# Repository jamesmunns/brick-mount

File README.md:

# Brick Boards

Boards designed to be compatible with LEGO and other plastic building blocks.

There are KiCAD footprints for a variety of different brick arrangements in [the parts folder](./parts/brick-4_9id-6_0od.pretty/). I've also included a number of personal projects using these footprints in the `boards/` folder.

## LICENSE

The contents of the `parts/brick-4_9id-6_0od.pretty/` folder are licensed under a CC0 license.

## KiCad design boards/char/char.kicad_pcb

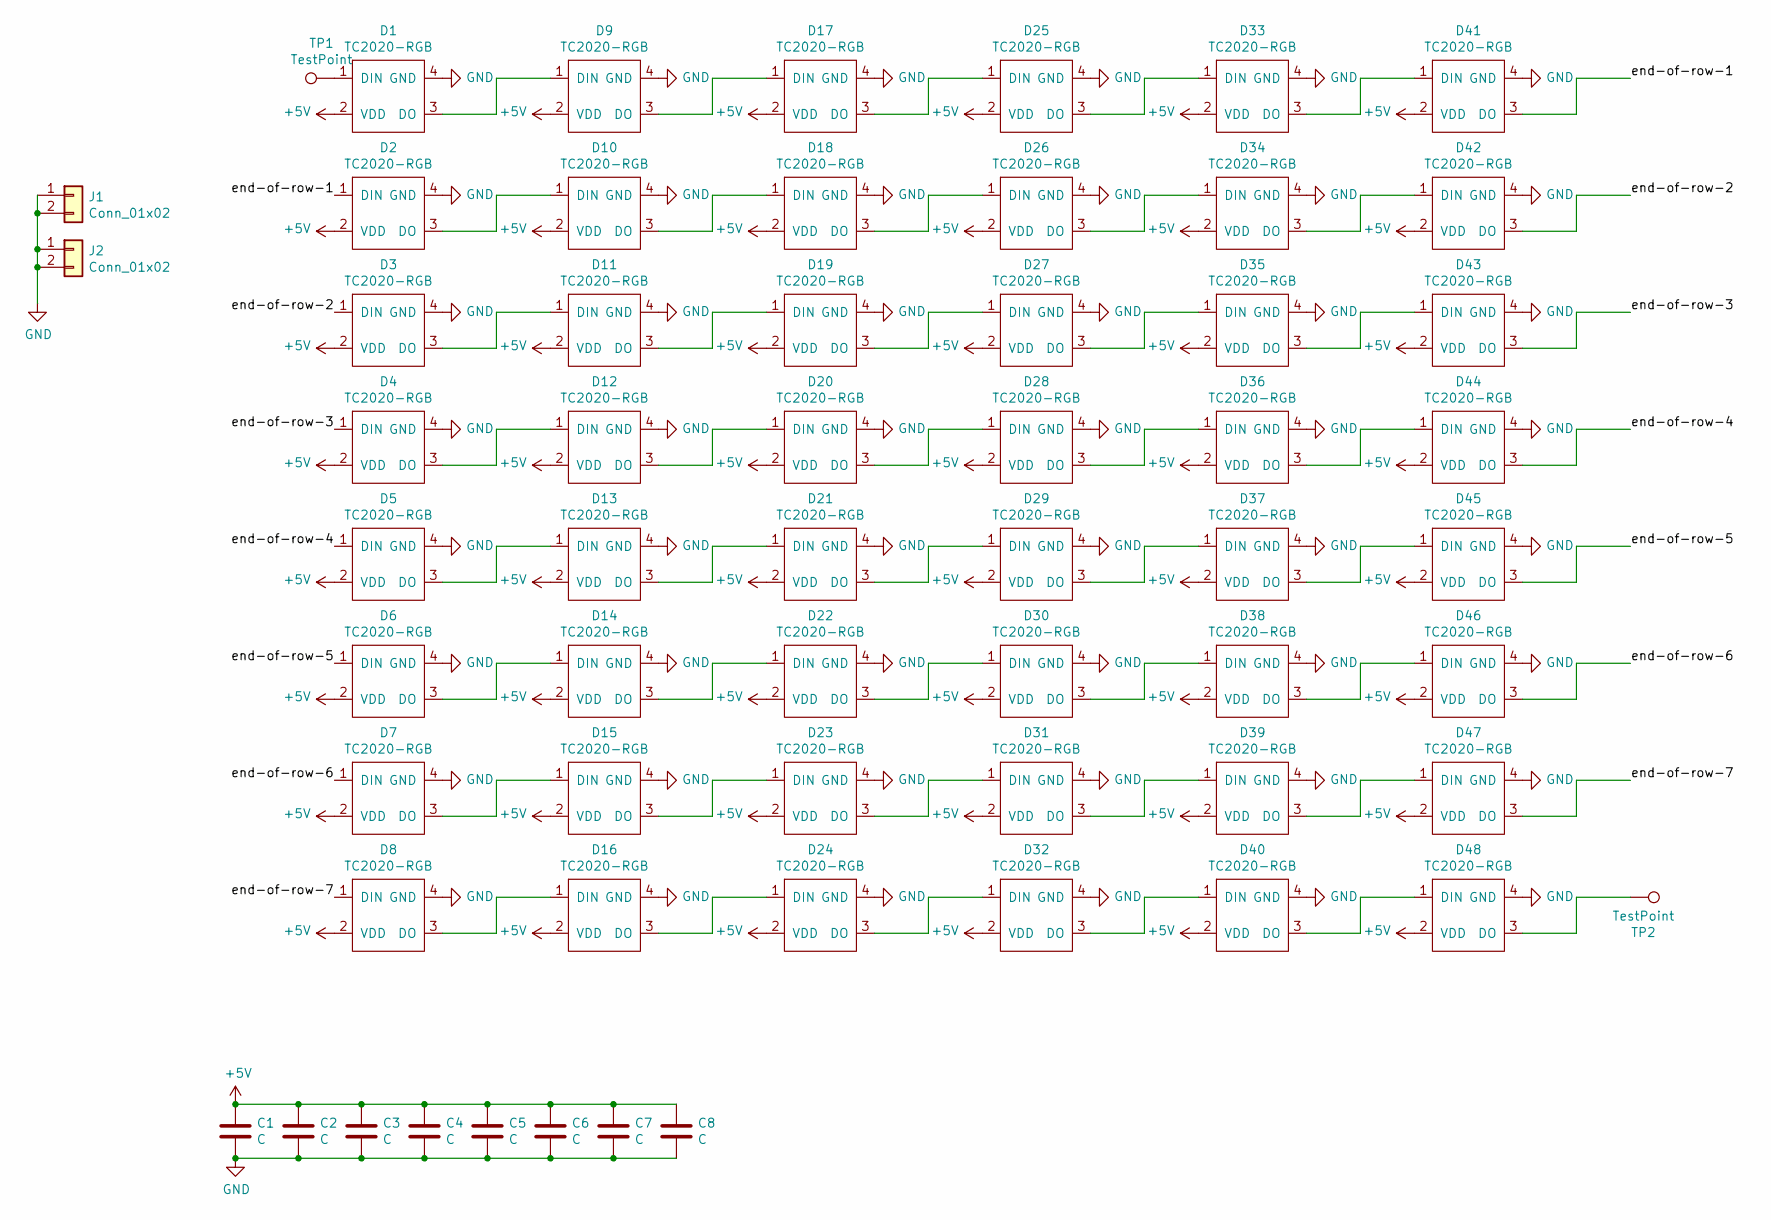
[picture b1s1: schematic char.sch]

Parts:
C1, C2, C3, C4, C5, C6, C7, C8: C; C_0805_2012Metric_Pad1.18x1.45mm_HandSolder
D1, D2, D3, D4, D5, D6, D7, D8, D9, D10, D11, D12, D13, D14, D15, D16, D17, D18, D19, D20, D21, D22, D23, D24, D25, D26, D27, D28, D29, D30, D31, D32, D33, D34, D35, D36, D37, D38, D39, D40, D41, D42, D43, D44, D45, D46, D47, D48: TC2020-RGB; TC2020RGB
J1, J2: Conn_01x02; brick-1x2
TP1, TP2: TestPoint; TestPoint_Pad_D1.5mm

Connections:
+5V: C1.1, C2.1, C3.1, C4.1, C5.1, C6.1, C7.1, C8.1, D1.2 (VDD), D2.2 (VDD), D3.2 (VDD), D4.2 (VDD), D5.2 (VDD), D6.2 (VDD), D7.2 (VDD), D8.2 (VDD), D9.2 (VDD), D10.2 (VDD), D11.2 (VDD), D12.2 (VDD), D13.2 (VDD), D14.2 (VDD), D15.2 (VDD), D16.2 (VDD), D17.2 (VDD), D18.2 (VDD), D19.2 (VDD), D20.2 (VDD), D21.2 (VDD), D22.2 (VDD), D23.2 (VDD), D24.2 (VDD), D25.2 (VDD), D26.2 (VDD), D27.2 (VDD), D28.2 (VDD), D29.2 (VDD), D30.2 (VDD), D31.2 (VDD), D32.2 (VDD), D33.2 (VDD), D34.2 (VDD), D35.2 (VDD), D36.2 (VDD), D37.2 (VDD), D38.2 (VDD), D39.2 (VDD), D40.2 (VDD), D41.2 (VDD), D42.2 (VDD), D43.2 (VDD), D44.2 (VDD), D45.2 (VDD), D46.2 (VDD), D47.2 (VDD), D48.2 (VDD)
/end-of-row-1: D2.1 (DIN), D41.3 (DO)
/end-of-row-2: D3.1 (DIN), D42.3 (DO)
/end-of-row-3: D4.1 (DIN), D43.3 (DO)
/end-of-row-4: D5.1 (DIN), D44.3 (DO)
/end-of-row-5: D6.1 (DIN), D45.3 (DO)
/end-of-row-6: D7.1 (DIN), D46.3 (DO)
/end-of-row-7: D8.1 (DIN), D47.3 (DO)
GND: C1.2, C2.2, C3.2, C4.2, C5.2, C6.2, C7.2, C8.2, D1.4 (GND), D2.4 (GND), D3.4 (GND), D4.4 (GND), D5.4 (GND), D6.4 (GND), D7.4 (GND), D8.4 (GND), D9.4 (GND), D10.4 (GND), D11.4 (GND), D12.4 (GND), D13.4 (GND), D14.4 (GND), D15.4 (GND), D16.4 (GND), D17.4 (GND), D18.4 (GND), D19.4 (GND), D20.4 (GND), D21.4 (GND), D22.4 (GND), D23.4 (GND), D24.4 (GND), D25.4 (GND), D26.4 (GND), D27.4 (GND), D28.4 (GND), D29.4 (GND), D30.4 (GND), D31.4 (GND), D32.4 (GND), D33.4 (GND), D34.4 (GND), D35.4 (GND), D36.4 (GND), D37.4 (GND), D38.4 (GND), D39.4 (GND), D40.4 (GND), D41.4 (GND), D42.4 (GND), D43.4 (GND), D44.4 (GND), D45.4 (GND), D46.4 (GND), D47.4 (GND), D48.4 (GND), J1.1, J1.2, J2.1, J2.2
unnamed: D1.1 (DIN), TP1.1
unnamed: D1.3 (DO), D9.1 (DIN)
unnamed: D2.3 (DO), D10.1 (DIN)
unnamed: D10.3 (DO), D18.1 (DIN)
unnamed: D3.3 (DO), D11.1 (DIN)
unnamed: D11.3 (DO), D19.1 (DIN)
unnamed: D4.3 (DO), D12.1 (DIN)
unnamed: D12.3 (DO), D20.1 (DIN)
unnamed: D5.3 (DO), D13.1 (DIN)
unnamed: D13.3 (DO), D21.1 (DIN)
unnamed: D6.3 (DO), D14.1 (DIN)
unnamed: D14.3 (DO), D22.1 (DIN)
unnamed: D7.3 (DO), D15.1 (DIN)
unnamed: D15.3 (DO), D23.1 (DIN)
unnamed: D8.3 (DO), D16.1 (DIN)
unnamed: D16.3 (DO), D24.1 (DIN)
unnamed: D9.3 (DO), D17.1 (DIN)
unnamed: D17.3 (DO), D25.1 (DIN)
unnamed: D18.3 (DO), D26.1 (DIN)
unnamed: D19.3 (DO), D27.1 (DIN)
unnamed: D20.3 (DO), D28.1 (DIN)
unnamed: D21.3 (DO), D29.1 (DIN)
unnamed: D22.3 (DO), D30.1 (DIN)
unnamed: D23.3 (DO), D31.1 (DIN)
unnamed: D24.3 (DO), D32.1 (DIN)
unnamed: D25.3 (DO), D33.1 (DIN)
unnamed: D26.3 (DO), D34.1 (DIN)
unnamed: D27.3 (DO), D35.1 (DIN)
unnamed: D28.3 (DO), D36.1 (DIN)
unnamed: D29.3 (DO), D37.1 (DIN)
unnamed: D30.3 (DO), D38.1 (DIN)
unnamed: D31.3 (DO), D39.1 (DIN)
unnamed: D32.3 (DO), D40.1 (DIN)
unnamed: D33.3 (DO), D41.1 (DIN)
unnamed: D34.3 (DO), D42.1 (DIN)
unnamed: D35.3 (DO), D43.1 (DIN)
unnamed: D36.3 (DO), D44.1 (DIN)
unnamed: D37.3 (DO), D45.1 (DIN)
unnamed: D38.3 (DO), D46.1 (DIN)
unnamed: D39.3 (DO), D47.1 (DIN)
unnamed: D40.3 (DO), D48.1 (DIN)
unnamed: D48.3 (DO), TP2.1

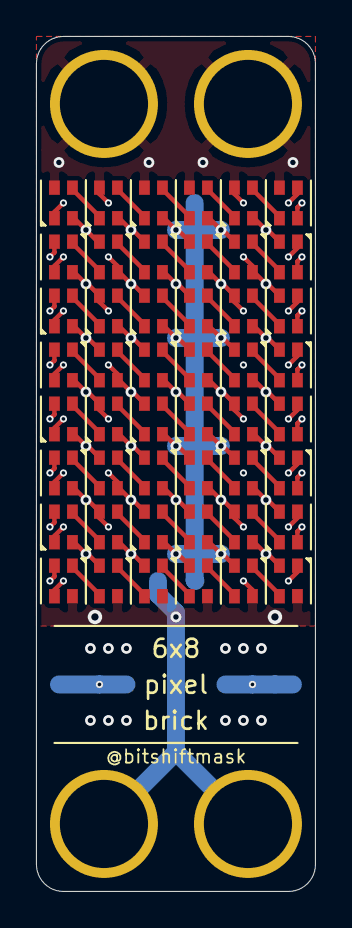
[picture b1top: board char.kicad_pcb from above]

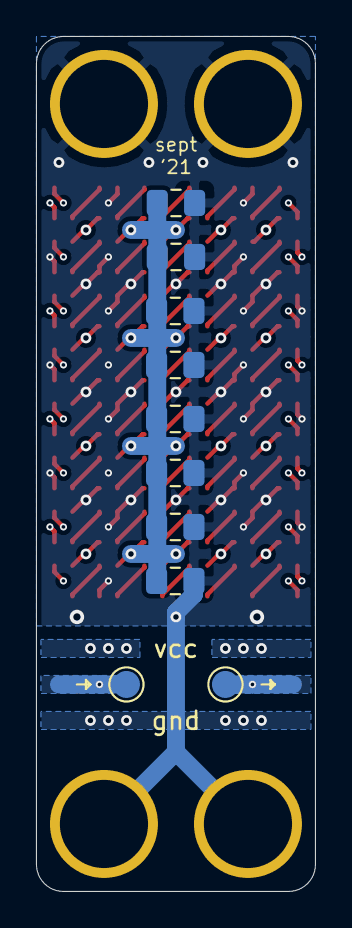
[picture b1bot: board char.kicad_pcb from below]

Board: 4 copper layers, 15.5 x 47.5 mm, 60 parts (10 on the bottom side), 51 nets.

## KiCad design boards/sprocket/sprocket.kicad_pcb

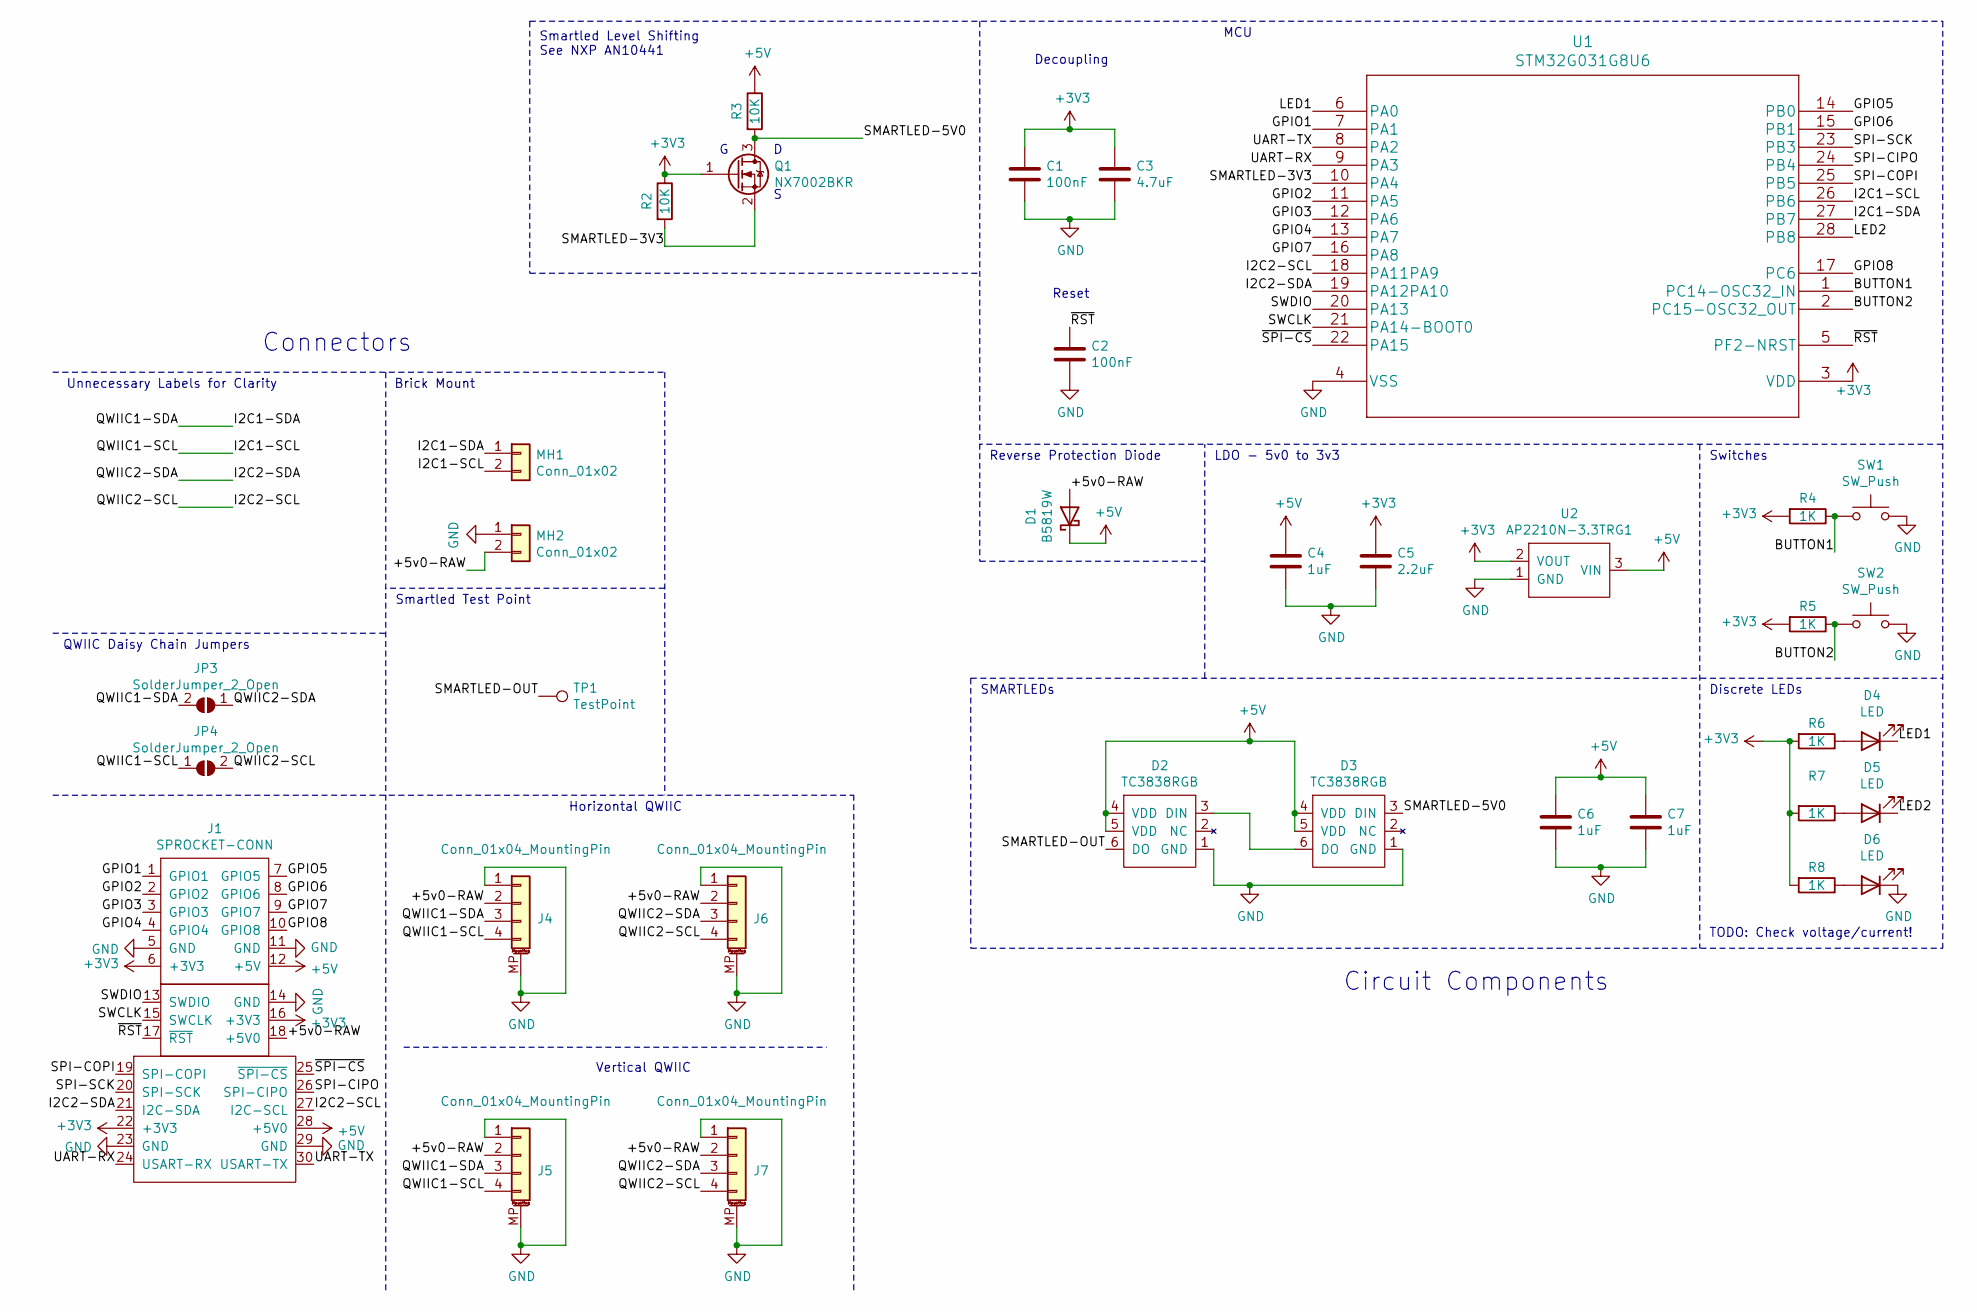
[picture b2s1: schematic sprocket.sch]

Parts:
C1, C2: 100nF; C_0402_1005Metric
C3: 4.7uF; C_0402_1005Metric
C4, C6, C7: 1uF; C_0402_1005Metric
C5: 2.2uF; C_0603_1608Metric
D1: B5819W; D_SOD-123
D2, D3: TC3838RGB
D4, D5, D6: LED; D_0603_1608Metric
J1: SPROCKET-CONN; sprocket-pins
J4, J6: Conn_01x04_MountingPin; JST_SH_SM04B-SRSS-TB_1x04-1MP_P1.00mm_Horizontal
J5, J7: Conn_01x04_MountingPin; JST_SH_BM04B-SRSS-TB_1x04-1MP_P1.00mm_Vertical
JP3, JP4: SolderJumper_2_Open; SolderJumper-2_P1.3mm_Open_RoundedPad1.0x1.5mm
MH1, MH2: Conn_01x02; brick-1x2
Q1: NX7002BKR; SOT-23
R2, R3: 10K; R_0402_1005Metric
R4, R5, R6, R7, R8: 1K; R_0402_1005Metric
SW1, SW2: SW_Push; K2-1808SN-A4SW-01
TP1: TestPoint; TestPoint_Pad_D1.5mm
U1: STM32G031G8U6
U2: AP2210N-3.3TRG1; SOT-23

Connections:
+3V3: C1.1, C3.1, C5.1, J1.6 (+3V3), J1.16 (+3V3), J1.22 (+3V3), Q1.1 (G), R2.1, R4.2, R5.2, R6.2, R7.2, R8.2, U1.3 (VDD), U2.2 (VOUT)
+5V: C4.1, C6.1, C7.1, D1.1 (K), D2.4 (VDD), D2.5 (VDD), D3.4 (VDD), D3.5 (VDD), J1.12 (+5V), J1.28 (+5V0), R3.1, U2.3 (VIN)
/+5v0-RAW: D1.2 (A), J1.18 (+5V0), J4.2, J5.2, J6.2, J7.2, MH2.2
/BUTTON1: R4.1, SW1.1, U1.1 (PC14-OSC32_IN)
/BUTTON2: R5.1, SW2.1, U1.2 (PC15-OSC32_OUT)
/GPIO1: J1.1 (GPIO1), U1.7 (PA1)
/GPIO2: J1.2 (GPIO2), U1.11 (PA5)
/GPIO3: J1.3 (GPIO3), U1.12 (PA6)
/GPIO4: J1.4 (GPIO4), U1.13 (PA7)
/GPIO5: J1.7 (GPIO5), U1.14 (PB0)
/GPIO6: J1.8 (GPIO6), U1.15 (PB1)
/GPIO7: J1.9 (GPIO7), U1.16 (PA8)
/GPIO8: J1.10 (GPIO8), U1.17 (PC6)
/I2C1-SCL: J4.4, J5.4, JP4.1 (A), MH1.2, U1.26 (PB6)
/I2C1-SDA: J4.3, J5.3, JP3.2 (B), MH1.1, U1.27 (PB7)
/I2C2-SCL: J1.27 (I2C-SCL), J6.4, J7.4, JP4.2 (B), U1.18 (PA11PA9)
/I2C2-SDA: J1.21 (I2C-SDA), J6.3, J7.3, JP3.1 (A), U1.19 (PA12PA10)
/LED1: D4.1 (K), U1.6 (PA0)
/LED2: D5.1 (K), U1.28 (PB8)
/SMARTLED-3V3: Q1.2 (S), R2.2, U1.10 (PA4)
/SMARTLED-5V0: D3.3 (DIN), Q1.3 (D), R3.2
/SMARTLED-OUT: D2.6 (DO), TP1.1
/SPI-CIPO: J1.26 (SPI-CIPO), U1.24 (PB4)
/SPI-COPI: J1.19 (SPI-COPI), U1.25 (PB5)
/SPI-SCK: J1.20 (SPI-SCK), U1.23 (PB3)
/SWCLK: J1.15 (SWCLK), U1.21 (PA14-BOOT0)
/SWDIO: J1.13 (SWDIO), U1.20 (PA13)
/UART-RX: J1.24 (USART-RX), U1.9 (PA3)
/UART-TX: J1.30 (USART-TX), U1.8 (PA2)
/~RST: C2.1, J1.17 (~RST), U1.5 (PF2-NRST)
/~SPI-CS: J1.25 (~SPI-CS), U1.22 (PA15)
GND: C1.2, C2.2, C3.2, C4.2, C5.2, C6.2, C7.2, D2.1 (GND), D3.1 (GND), D6.1 (K), J1.5 (GND), J1.11 (GND), J1.14 (GND), J1.23 (GND), J1.29 (GND), J4.1, J4.MP (MountPin), J5.1, J5.MP (MountPin), J6.1, J6.MP (MountPin), J7.1, J7.MP (MountPin), MH2.1, SW1.2, SW2.2, U1.4 (VSS), U2.1 (GND)
unnamed: D2.3 (DIN), D3.6 (DO)
unnamed: D4.2 (A), R6.1
unnamed: D5.2 (A), R7.1
unnamed: D6.2 (A), R8.1

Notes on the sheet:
Decoupling
Reset
MCU
Switches
LDO - 5v0 to 3v3
Reverse Protection Diode
Discrete LEDs
TODO: Check voltage/current!
SMARTLEDs
Smartled Level Shifting See NXP AN10441
Horizontal QWIIC
Vertical QWIIC
QWIIC Daisy Chain Jumpers
Unnecessary Labels for Clarity
Brick Mount
Connectors
Circuit Components
Smartled Test Point

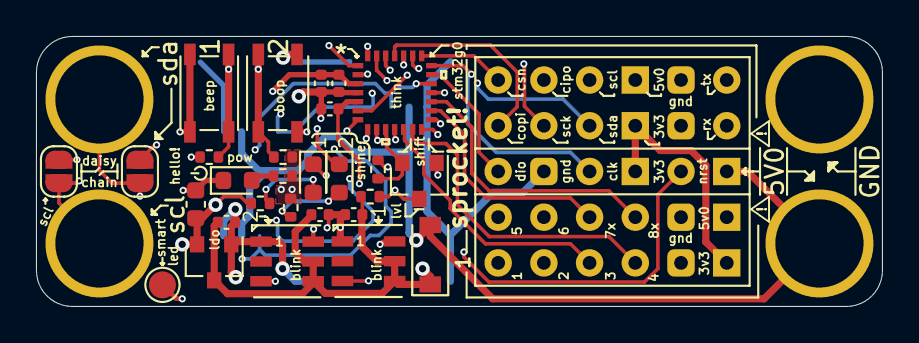
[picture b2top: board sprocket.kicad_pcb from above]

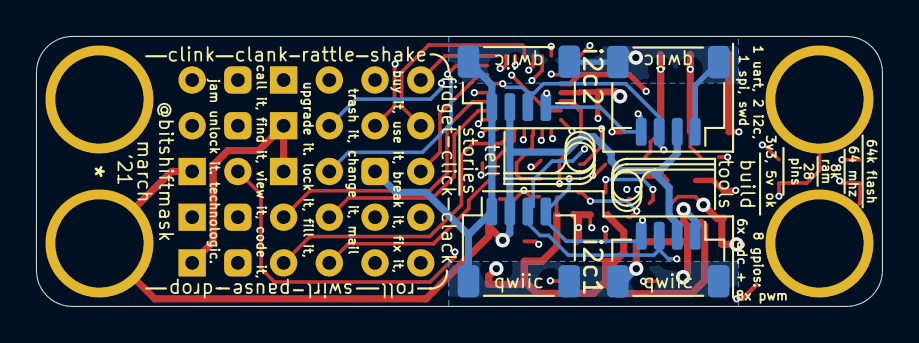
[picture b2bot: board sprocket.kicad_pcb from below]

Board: 4 copper layers, 47.0 x 15.0 mm, 35 parts (4 on the bottom side), 36 nets.

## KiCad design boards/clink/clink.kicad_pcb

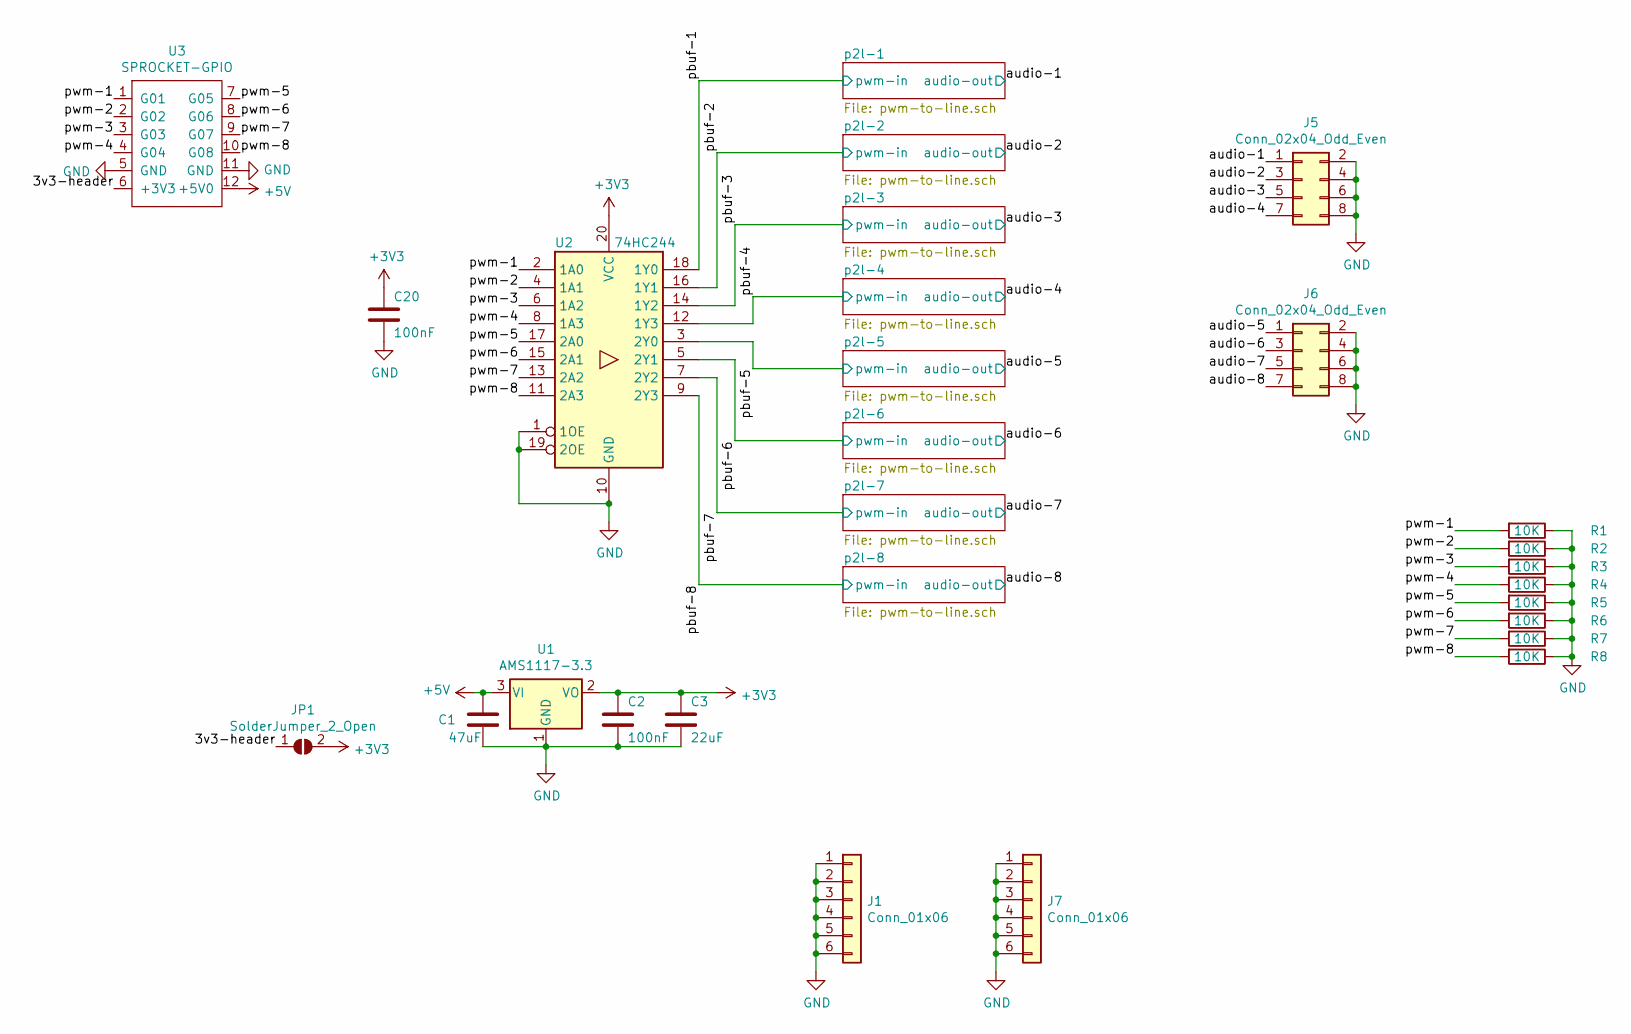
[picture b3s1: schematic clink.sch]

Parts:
C1: 47uF; C_1206_3216Metric
C2, C20: 100nF; C_0402_1005Metric
C3: 22uF; C_0805_2012Metric
J1, J7: Conn_01x06; brick-1x6
J5, J6: Conn_02x04_Odd_Even; PinSocket_2x04_P2.54mm_Vertical
JP1: SolderJumper_2_Open; SolderJumper-2_P1.3mm_Open_TrianglePad1.0x1.5mm
R1, R2, R3, R4, R5, R6, R7, R8: 10K; R_0402_1005Metric
U1: AMS1117-3.3; SOT-223-3_TabPin2
U2: 74HC244; SOIC-20W_7.5x12.8mm_P1.27mm
U3: SPROCKET-GPIO

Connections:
+3V3: C2.1, C3.1, C20.1, JP1.2 (B), U1.2 (VO), U2.20 (VCC)
+5V: C1.1, U1.3 (VI), U3.12 (+5V0)
/3v3-header: JP1.1 (A), U3.6 (+3V3)
/audio-1: J5.1; also elsewhere on the board
/audio-2: J5.3; also elsewhere on the board
/audio-3: J5.5; also elsewhere on the board
/audio-4: J5.7; also elsewhere on the board
/audio-5: J6.1; also elsewhere on the board
/audio-6: J6.3; also elsewhere on the board
/audio-7: J6.5; also elsewhere on the board
/audio-8: J6.7; also elsewhere on the board
/pbuf-1: U2.18 (1Y0); also elsewhere on the board
/pbuf-2: U2.16 (1Y1); also elsewhere on the board
/pbuf-3: U2.14 (1Y2); also elsewhere on the board
/pbuf-4: U2.12 (1Y3); also elsewhere on the board
/pbuf-5: U2.3 (2Y0); also elsewhere on the board
/pbuf-6: U2.5 (2Y1); also elsewhere on the board
/pbuf-7: U2.7 (2Y2); also elsewhere on the board
/pbuf-8: U2.9 (2Y3); also elsewhere on the board
/pwm-1: R1.2, U2.2 (1A0), U3.1 (G01)
/pwm-2: R2.2, U2.4 (1A1), U3.2 (G02)
/pwm-3: R3.2, U2.6 (1A2), U3.3 (G03)
/pwm-4: R4.2, U2.8 (1A3), U3.4 (G04)
/pwm-5: R5.2, U2.17 (2A0), U3.7 (G05)
/pwm-6: R6.2, U2.15 (2A1), U3.8 (G06)
/pwm-7: R7.2, U2.13 (2A2), U3.9 (G07)
/pwm-8: R8.2, U2.11 (2A3), U3.10 (G08)
GND: C1.2, C2.2, C3.2, C20.2, J1.1, J1.2, J1.3, J1.4, J1.5, J1.6, J5.2, J5.4, J5.6, J5.8, J6.2, J6.4, J6.6, J6.8, J7.1, J7.2, J7.3, J7.4, J7.5, J7.6, R1.1, R2.1, R3.1, R4.1, R5.1, R6.1, R7.1, R8.1, U1.1 (GND), U2.1 (1OE), U2.10 (GND), U2.19 (2OE), U3.5 (GND), U3.11 (GND); also elsewhere on the board

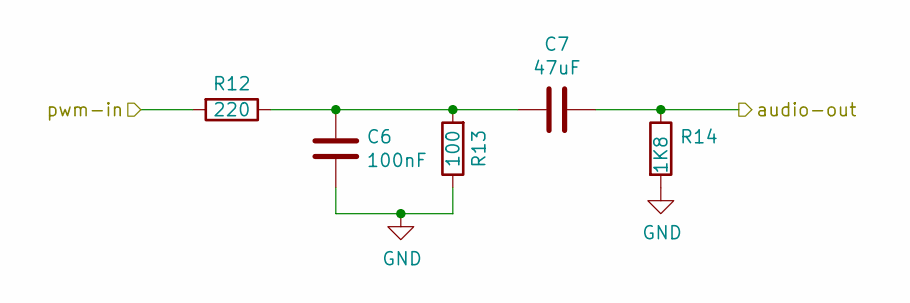
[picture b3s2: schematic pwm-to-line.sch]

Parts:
C4: 100nF; C_0402_1005Metric
C5: 47uF; C_1206_3216Metric
R9: 220; R_0805_2012Metric
R10: 100; R_0805_2012Metric
R11: 1K8; R_0805_2012Metric

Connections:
/audio-1: C5.1, R11.1; also elsewhere on the board
/pbuf-1: R9.2; also elsewhere on the board
GND: C4.2, R10.1, R11.2; also elsewhere on the board
unnamed: C4.1, C5.2, R9.1, R10.2

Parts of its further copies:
C6, C8, C10, C12, C14, C16, C18: 100nF; C_0402_1005Metric
C7, C9, C11, C13, C15, C17, C19: 47uF; C_1206_3216Metric
R12, R15, R18, R21, R24, R27, R30: 220; R_0805_2012Metric
R13, R16, R19, R22, R25, R28, R31: 100; R_0805_2012Metric
R14, R17, R20, R23, R26, R29, R32: 1K8; R_0805_2012Metric

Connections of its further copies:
/audio-2: C7.1, R14.1; also elsewhere on the board
/audio-3: C9.1, R17.1; also elsewhere on the board
/audio-4: C11.1, R20.1; also elsewhere on the board
/audio-5: C13.1, R23.1; also elsewhere on the board
/audio-6: C15.1, R26.1; also elsewhere on the board
/audio-7: C17.1, R29.1; also elsewhere on the board
/audio-8: C19.1, R32.1; also elsewhere on the board
/pbuf-2: R12.2; also elsewhere on the board
/pbuf-3: R15.2; also elsewhere on the board
/pbuf-4: R18.2; also elsewhere on the board
/pbuf-5: R21.2; also elsewhere on the board
/pbuf-6: R24.2; also elsewhere on the board
/pbuf-7: R27.2; also elsewhere on the board
/pbuf-8: R30.2; also elsewhere on the board
GND: C6.2, C8.2, C10.2, C12.2, C14.2, C16.2, C18.2, R13.1, R14.2, R16.1, R17.2, R19.1, R20.2, R22.1, R23.2, R25.1, R26.2, R28.1, R29.2, R31.1, R32.2; also elsewhere on the board
unnamed: C6.1, C7.2, R12.1, R13.2
unnamed: C8.1, C9.2, R15.1, R16.2
unnamed: C10.1, C11.2, R18.1, R19.2
unnamed: C12.1, C13.2, R21.1, R22.2
unnamed: C14.1, C15.2, R24.1, R25.2
unnamed: C16.1, C17.2, R27.1, R28.2
unnamed: C18.1, C19.2, R30.1, R31.2

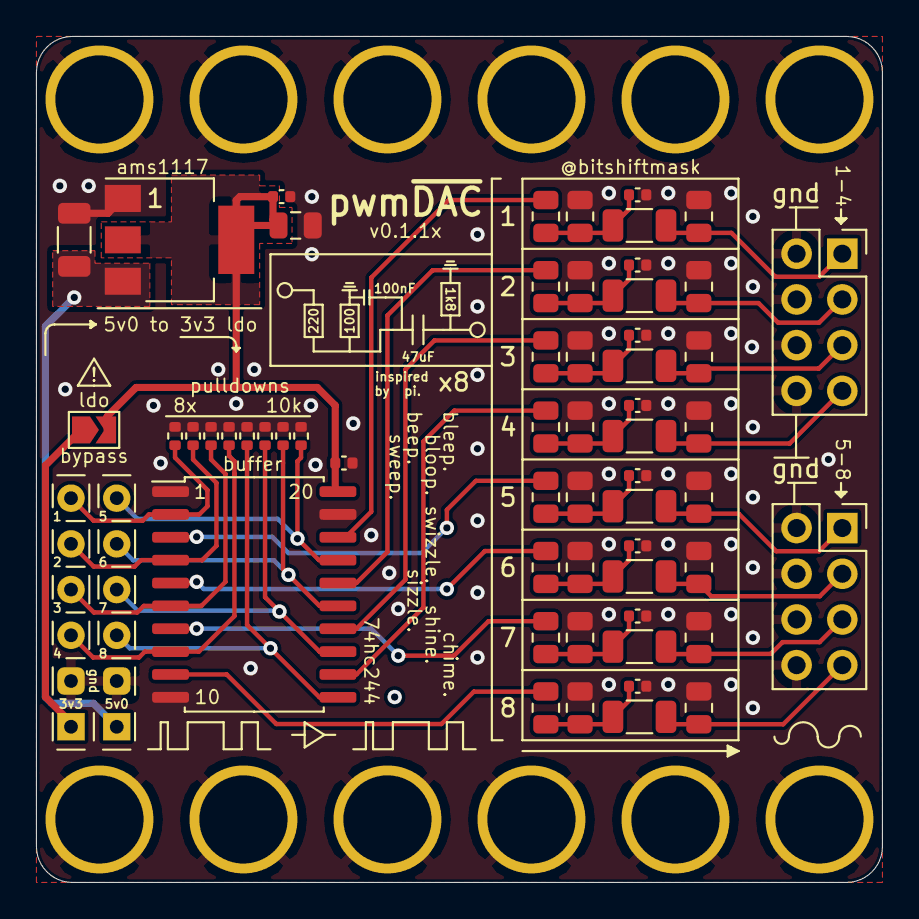
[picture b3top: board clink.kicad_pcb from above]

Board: 2 copper layers, 47.0 x 47.0 mm, 60 parts (0 on the bottom side), 36 nets.

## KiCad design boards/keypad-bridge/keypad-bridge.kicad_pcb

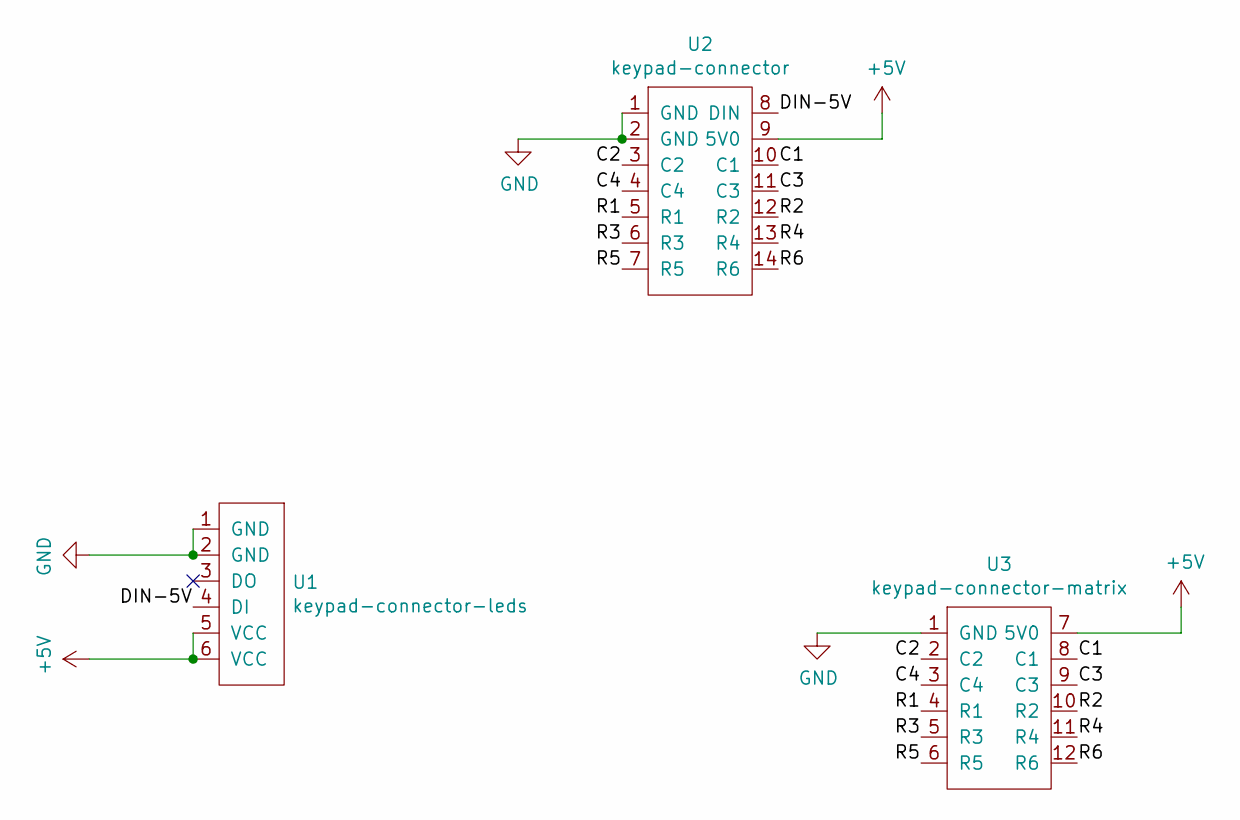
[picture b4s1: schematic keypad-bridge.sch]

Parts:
U1: keypad-connector-leds
U2: keypad-connector
U3: keypad-connector-matrix

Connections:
+5V: U1.5 (VCC), U1.6 (VCC), U2.9 (5V0), U3.7 (5V0)
/C1: U2.10 (C1), U3.8 (C1)
/C2: U2.3 (C2), U3.2 (C2)
/C3: U2.11 (C3), U3.9 (C3)
/C4: U2.4 (C4), U3.3 (C4)
/DIN-5V: U1.4 (DI), U2.8 (DIN)
/R1: U2.5 (R1), U3.4 (R1)
/R2: U2.12 (R2), U3.10 (R2)
/R3: U2.6 (R3), U3.5 (R3)
/R4: U2.13 (R4), U3.11 (R4)
/R5: U2.7 (R5), U3.6 (R5)
/R6: U2.14 (R6), U3.12 (R6)
GND: U1.1 (GND), U1.2 (GND), U2.1 (GND), U2.2 (GND), U3.1 (GND)

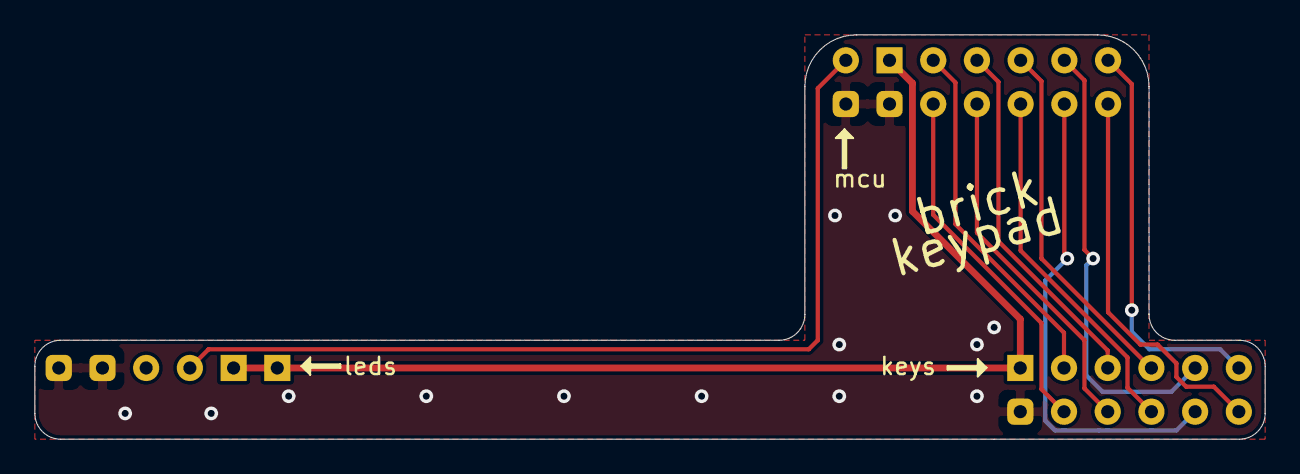
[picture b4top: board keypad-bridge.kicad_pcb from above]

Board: 2 copper layers, 71.5 x 23.5 mm, 3 parts (0 on the bottom side), 13 nets.

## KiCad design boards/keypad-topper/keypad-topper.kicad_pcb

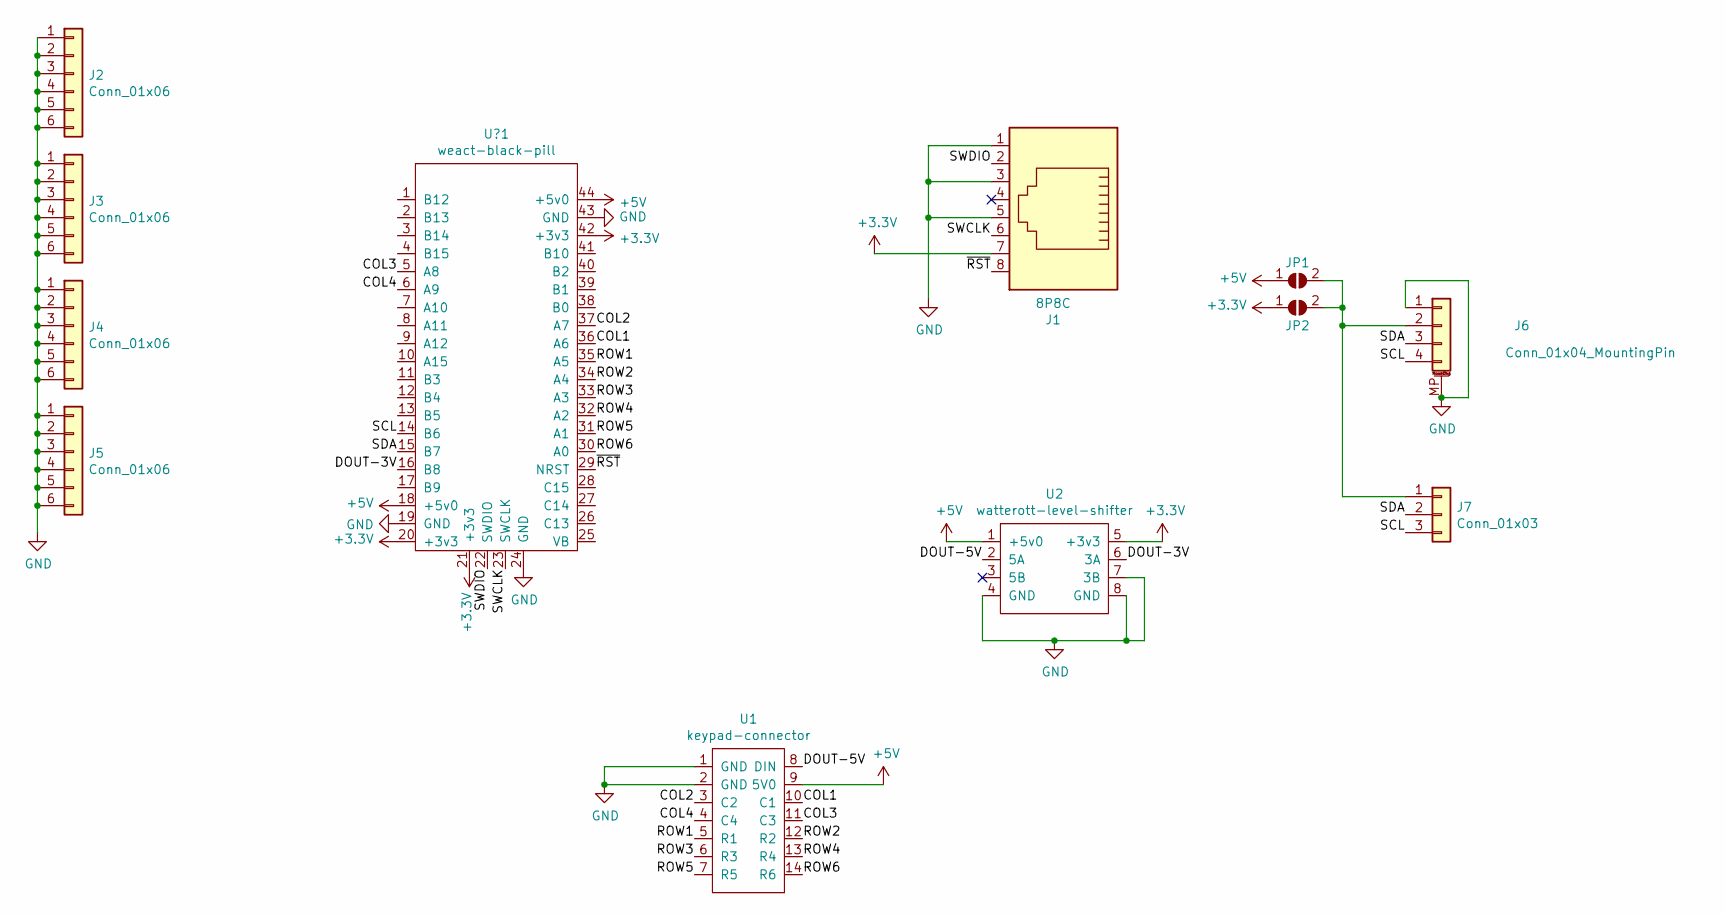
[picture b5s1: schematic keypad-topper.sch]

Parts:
J1: 8P8C; RJ45_Amphenol_54602-x08_Horizontal
J2, J3, J4, J5: Conn_01x06; brick-1x6
J6: Conn_01x04_MountingPin; JST_SH_SM04B-SRSS-TB_1x04-1MP_P1.00mm_Horizontal
J7: Conn_01x03; brick-1x3
JP1, JP2: SolderJumper_2_Open; SolderJumper-2_P1.3mm_Open_TrianglePad1.0x1.5mm
U1: keypad-connector
U2: watterott-level-shifter
U?1: weact-black-pill; weact-blackpill

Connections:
+3V3: J1.7, JP2.1 (A), U2.5 (+3v3), U?1.20 (+3v3), U?1.21 (+3v3), U?1.42 (+3v3)
+5V: JP1.1 (A), U1.9 (5V0), U2.1 (+5v0), U?1.18 (+5v0), U?1.44 (+5v0)
/COL1: U1.10 (C1), U?1.36 (A6)
/COL2: U1.3 (C2), U?1.37 (A7)
/COL3: U1.11 (C3), U?1.5 (A8)
/COL4: U1.4 (C4), U?1.6 (A9)
/DOUT-3V: U2.6 (3A), U?1.16 (B8)
/DOUT-5V: U1.8 (DIN), U2.2 (5A)
/ROW1: U1.5 (R1), U?1.35 (A5)
/ROW2: U1.12 (R2), U?1.34 (A4)
/ROW3: U1.6 (R3), U?1.33 (A3)
/ROW4: U1.13 (R4), U?1.32 (A2)
/ROW5: U1.7 (R5), U?1.31 (A1)
/ROW6: U1.14 (R6), U?1.30 (A0)
/SCL: J6.4, J7.3, U?1.14 (B6)
/SDA: J6.3, J7.2, U?1.15 (B7)
/SWCLK: J1.6, U?1.23 (SWCLK)
/SWDIO: J1.2, U?1.22 (SWDIO)
/~RST: J1.8, U?1.29 (NRST)
GND: J1.1, J1.3, J1.5, J2.1, J2.2, J2.3, J2.4, J2.5, J2.6, J3.1, J3.2, J3.3, J3.4, J3.5, J3.6, J4.1, J4.2, J4.3, J4.4, J4.5, J4.6, J5.1, J5.2, J5.3, J5.4, J5.5, J5.6, J6.1, J6.MP (MountPin), U1.1 (GND), U1.2 (GND), U2.4 (GND), U2.7 (3B), U2.8 (GND), U?1.19 (GND), U?1.24 (GND), U?1.43 (GND)
unnamed: J6.2, J7.1, JP1.2 (B), JP2.2 (B)

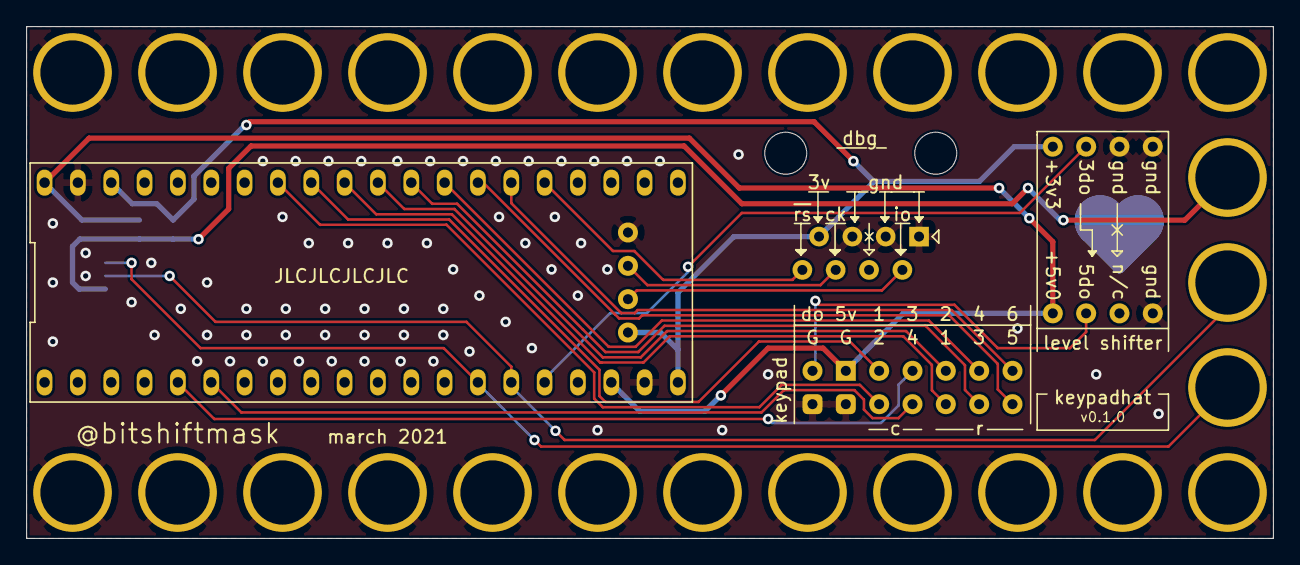
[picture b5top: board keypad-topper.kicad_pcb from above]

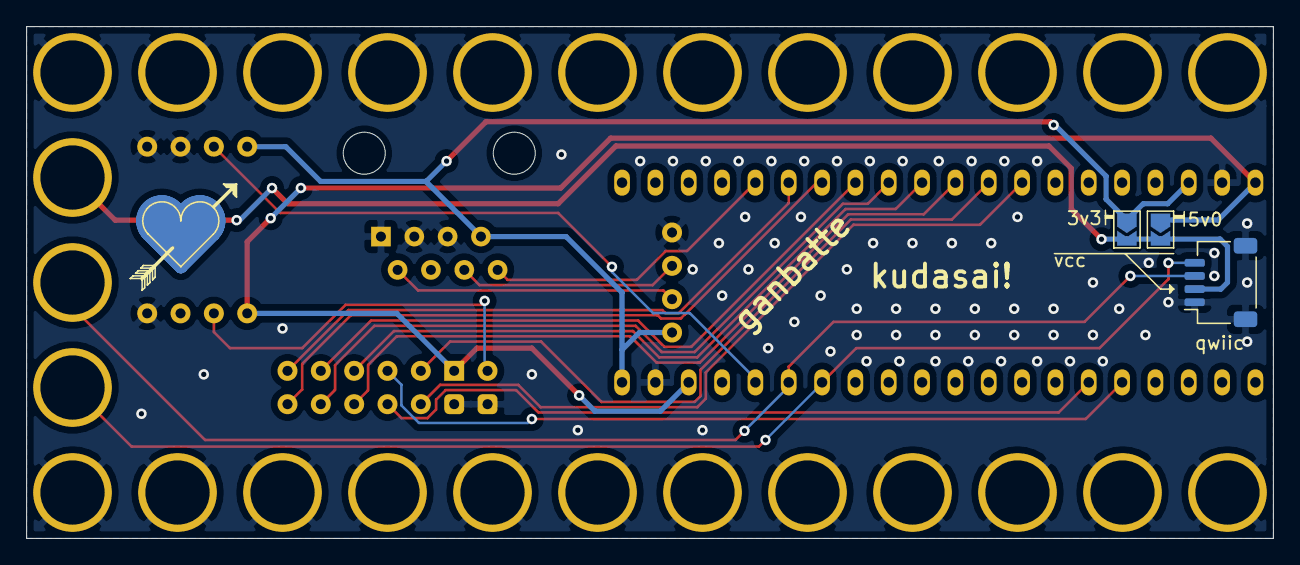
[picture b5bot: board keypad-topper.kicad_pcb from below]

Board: 2 copper layers, 95.0 x 39.0 mm, 12 parts (3 on the bottom side), 21 nets.

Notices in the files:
parts and their libraries:
Copyright 2016 Accelerated Designs. All rights reserved.
